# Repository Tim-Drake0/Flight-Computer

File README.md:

# Flight-Computer
Download and open bom.html for interactive BOM.

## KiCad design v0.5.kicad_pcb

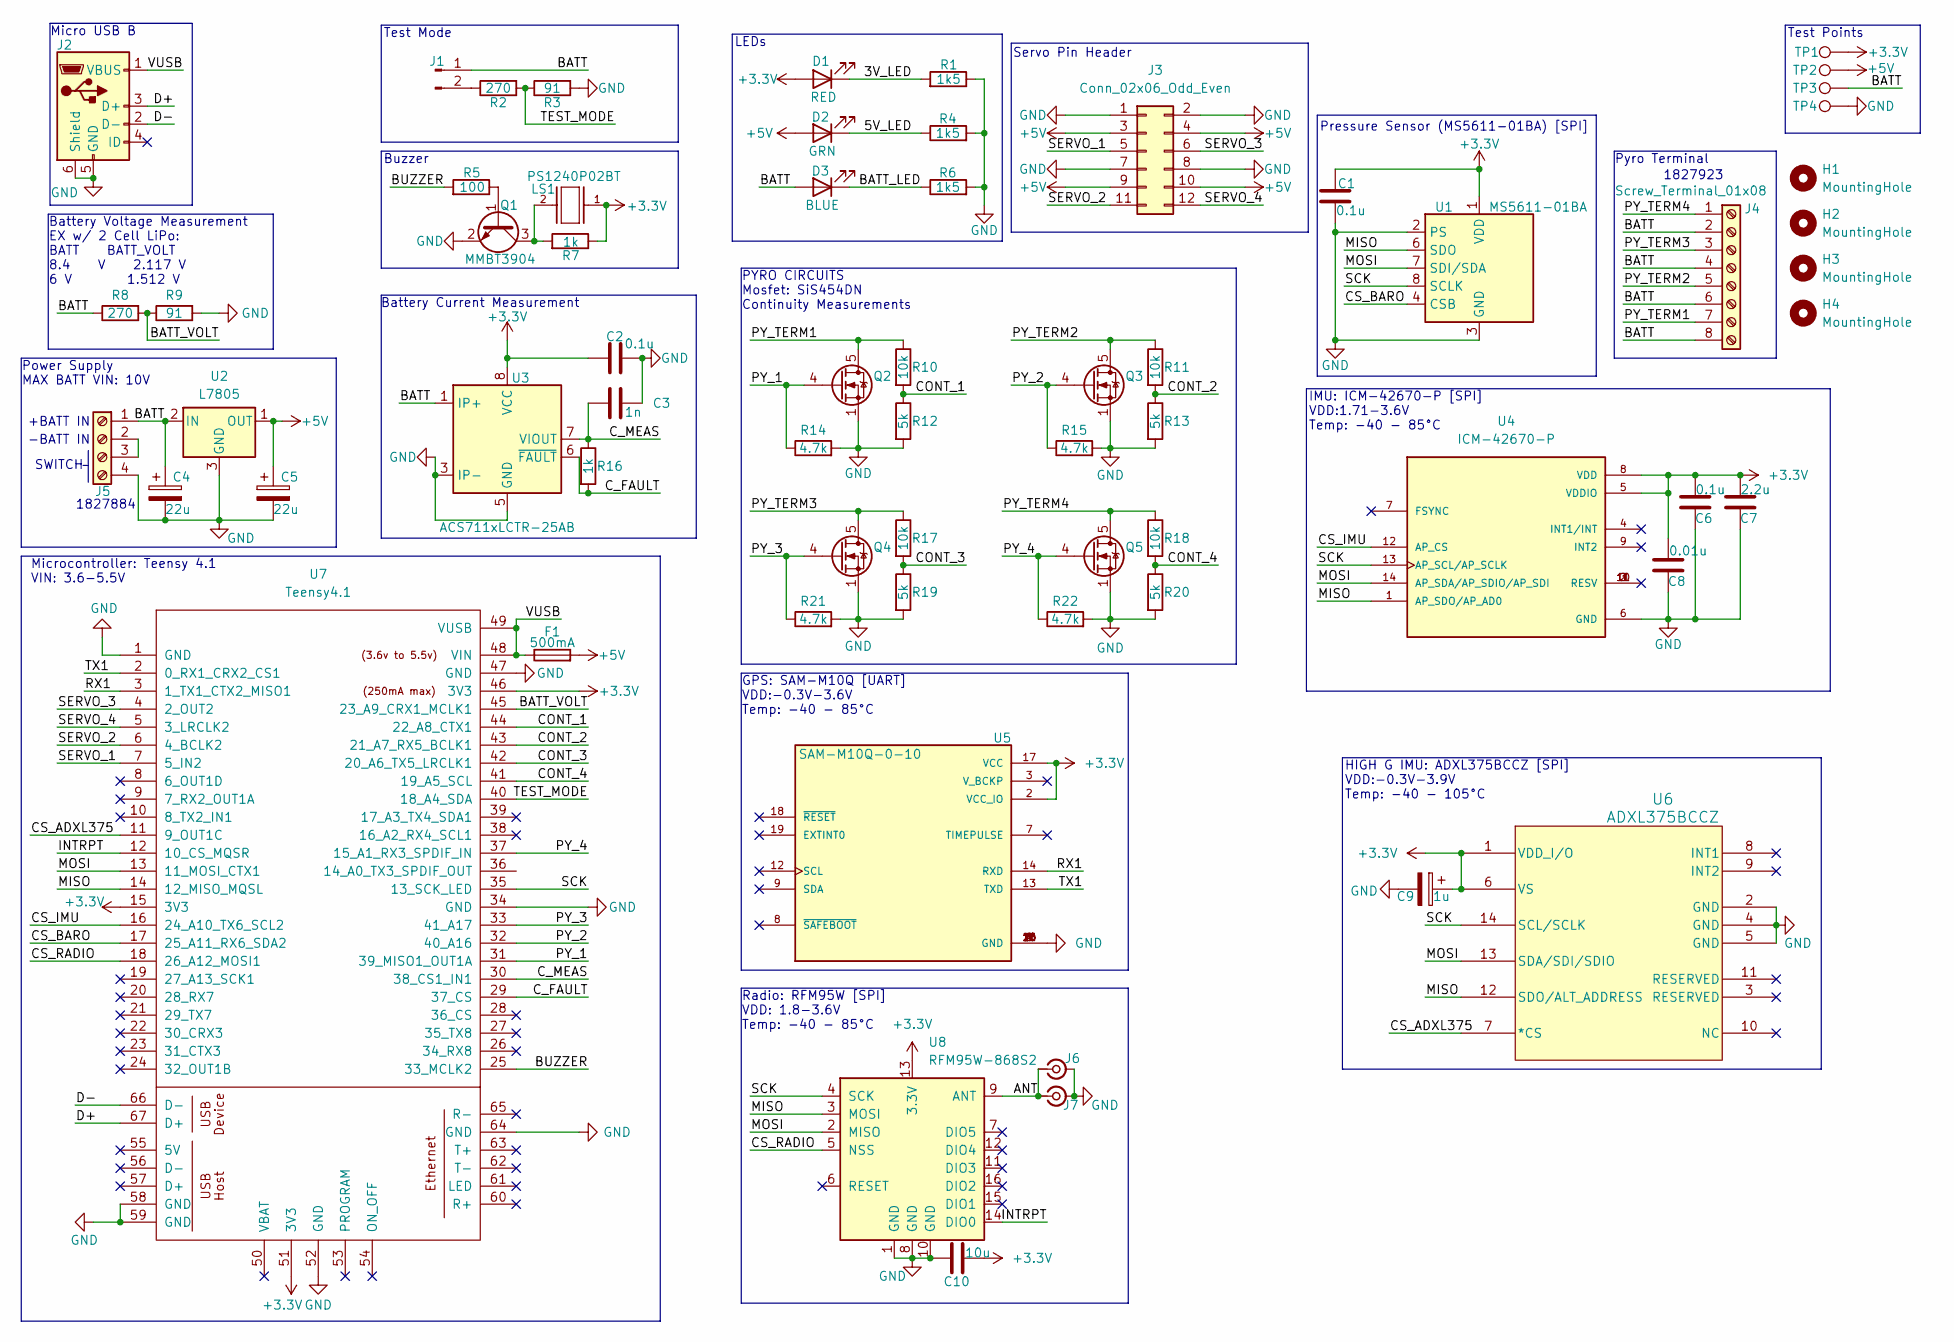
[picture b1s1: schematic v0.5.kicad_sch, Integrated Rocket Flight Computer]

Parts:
C1, C2, C6: 0.1u; C_0805_2012Metric; DigiKey CL21B104KBCNNNC
C3: 1n; C_0805_2012Metric; DigiKey CL21B102KCANNNC
C4, C5: 22u; C_0805_2012Metric; DigiKey TLJN226M010R3800
C7: 2.2u; C_0805_2012Metric; DigiKey CL21B225KPFNNNE
C8: 0.01u; C_0805_2012Metric; DigiKey CL21B103KBANNNC
C9: 1u; C_0805_2012Metric; DigiKey TAJR105K010RNJ
C10: 10u; C_0805_2012Metric_Pad1.18x1.45mm_HandSolder; DigiKey CL21A106KOQNNNE
D1: RED; LED_0603_1608Metric; DigiKey 150060RS75000
D2: GRN; LED_0603_1608Metric; DigiKey 150060GS75000
D3: BLUE; LED_0603_1608Metric; DigiKey 150060BS75000
F1: 500mA; Fuse_0805_2012Metric_Pad1.15x1.40mm_HandSolder; DigiKey F0805B0R50FSTR
H1, H2, H3, H4: MountingHole; MountingHole_2.2mm_M2
J1: Conn_01x02_Pin; PinHeader_1x02_P1.27mm_Horizontal; DigiKey M50-3930242, HMSC-G
J2: USB_B_Micro; USB_Micro-B_Amphenol_10118193-0001LF_Horizontal; DigiKey 10118193-0001LF
J3: Conn_02x06_Odd_Even; PinHeader_2x06_P2.54mm_Vertical; DigiKey PH2-12-UA
J4: Screw_Terminal_01x08; PhoenixContact_MC_1,5_8-GF-3.5_1x08_P3.50mm_Horizontal_Thre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
J5: Screw_Terminal_01x04; PhoenixContact_MC_1,5_4-GF-3.5_1x04_P3.50mm_Horizontal_Thre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
J6: Conn_Coaxial_Small; U.FL_Hirose_U.FL-R-SMT-1_Vertical
J7: Conn_Coaxial_Small; SMA_Samtec_SMA-J-P-H-ST-EM1_EdgeMount
LS1: PS1240P02BT; XDCR_PS1240P02BT; DigiKey PS1240P02BT
Q1: MMBT3904; SOT-23; DigiKey MMBT3904-7-F
Q2, Q3, Q4, Q5: SiS454DN; Vishay_PowerPAK_1212-8_Single; DigiKey SIS454DN-T1-GE3
R1, R4: 1k5; R_0805_2012Metric
R2, R8: 270; R_0805_2012Metric; DigiKey RC0805JR-07270RL
R3, R9: 91; R_0805_2012Metric; DigiKey RC0805FR-0791RL
R5: 100; R_0805_2012Metric; DigiKey RC0805FR-07100RL
R6: 1k5; R_0805_2012Metric; DigiKey RC0805FR-071K5L
R7, R16: 1k; R_0805_2012Metric; DigiKey RC0805FR-071KL
R10, R11, R17, R18: 10k; R_0805_2012Metric_Pad1.20x1.40mm_HandSolder; DigiKey ERJ-6GEYJ103V
R12, R13, R19, R20: 5k; R_0805_2012Metric_Pad1.20x1.40mm_HandSolder; DigiKey CRCW08055K00JNTA
R14, R15, R21, R22: 4.7k; R_0805_2012Metric; DigiKey CRCW08054K70FKEAC
TP1, TP2, TP3, TP4: TestPoint; TestPoint_Keystone_5000-5004_Miniature; DigiKey 5001
U1: MS5611-01BA; LGA-8_3x5mm_P1.25mm; DigiKey MS5611-01BA
U2: L7805; D2PAK_STM; DigiKey L7805ABD2T-TR
U3: ACS711xLCTR-25AB; SOIC-8_3.9x4.9mm_P1.27mm; DigiKey ACS711KLCTR-25AB-T
U4: ICM-42670-P; XDCR_ICM-42670-P; PARTREV 1.1; DigiKey_Part_Number 1428-ICM-42670-PTR-ND
U5: SAM-M10Q-0-10; ublox_SAM-M8Q_HandSolder; PARTREV R07; DigiKey SAM-M10Q-00B
U6: ADXL375BCCZ; LGA_CC-14-1_ADI; DigiKey ADXL375BCCZ
U7: Teensy4.1; Teensy41
U8: RFM95W-868S2; HOPERF_RFM9XW_SMD

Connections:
+3.3V: C1.1, C2.1, C6.2, C7.2, C8.2, C9.1, C10.1, D1.2 (A), LS1.1, R7.1, TP1.1, U1.1 (VDD), U3.8 (VCC), U4.5 (VDDIO), U4.8 (VDD), U5.2 (VCC_IO), U5.17 (VCC), U6.1 (VDD_I/O), U6.6 (VS), U7.15 (3V3), U7.46 (3V3), U7.51 (3V3), U8.13 (3.3V)
+5V: C5.1, D2.2 (A), F1.2, J3.3, J3.4, J3.9, J3.10, TP2.1, U2.1 (OUT)
/3V_LED: D1.1 (K), R1.2
/5V_LED: D2.1 (K), R4.1
/ANT: J6.1 (In), J7.1 (In), U8.9 (ANT)
/BATT: C4.1, D3.2 (A), J1.1, J4.2, J4.4, J4.6, J4.8, J5.1, R8.1, TP3.1, U2.2 (IN), U3.1 (IP+), U3.2 (IP+)
/BATT_LED: D3.1 (K), R6.1
/BATT_VOLT: R8.2, R9.1, U7.45 (23_A9_CRX1_MCLK1)
/BUZZER: R5.2, U7.25 (33_MCLK2)
/CONT_1: R10.2, R12.1, U7.44 (22_A8_CTX1)
/CONT_2: R11.2, R13.1, U7.43 (21_A7_RX5_BCLK1)
/CONT_3: R17.2, R19.1, U7.42 (20_A6_TX5_LRCLK1)
/CONT_4: R18.2, R20.1, U7.41 (19_A5_SCL)
/CS_ADXL375: U6.7 (*CS), U7.11 (9_OUT1C)
/CS_BARO: U1.4 (CSB), U1.5 (CSB), U7.17 (25_A11_RX6_SDA2)
/CS_IMU: U4.12 (AP_CS), U7.16 (24_A10_TX6_SCL2)
/CS_RADIO: U7.18 (26_A12_MOSI1), U8.5 (NSS)
/C_FAULT: R16.2, U3.6 (~FAULT), U7.29 (37_CS)
/C_MEAS: C3.1, R16.1, U3.7 (VIOUT), U7.30 (38_CS1_IN1)
/D+: J2.3 (D+), U7.67 (D+)
/D-: J2.2 (D-), U7.66 (D-)
/INTRPT: U7.12 (10_CS_MQSR), U8.14 (DIO0)
/MISO: U1.6 (SDO), U4.1 (AP_SDO/AP_AD0), U6.12 (SDO/ALT_ADDRESS), U7.14 (12_MISO_MQSL), U8.3 (MOSI)
/MOSI: U1.7 (SDI/SDA), U4.14 (AP_SDA/AP_SDIO/AP_SDI), U6.13 (SDA/SDI/SDIO), U7.13 (11_MOSI_CTX1), U8.2 (MISO)
/PY_1: Q2.4 (G), R14.1, U7.31 (39_MISO1_OUT1A)
/PY_2: Q3.4 (G), R15.1, U7.32 (40_A16)
/PY_3: Q4.4 (G), R21.1, U7.33 (41_A17)
/PY_4: Q5.4 (G), R22.1, U7.37 (15_A1_RX3_SPDIF_IN)
/PY_TERM1: J4.7, Q2.5 (D), R10.1
/PY_TERM2: J4.5, Q3.5 (D), R11.1
/PY_TERM3: J4.3, Q4.5 (D), R17.1
/PY_TERM4: J4.1, Q5.5 (D), R18.1
/RX1: U5.14 (RXD), U7.3 (1_TX1_CTX2_MISO1)
/SCK: U1.8 (SCLK), U4.13 (AP_SCL/AP_SCLK), U6.14 (SCL/SCLK), U7.35 (13_SCK_LED), U8.4 (SCK)
/SERVO_1: J3.5, U7.7 (5_IN2)
/SERVO_2: J3.11, U7.6 (4_BCLK2)
/SERVO_3: J3.6, U7.4 (2_OUT2)
/SERVO_4: J3.12, U7.5 (3_LRCLK2)
/TEST_MODE: R2.2, R3.1, U7.40 (18_A4_SDA)
/TX1: U5.13 (TXD), U7.2 (0_RX1_CRX2_CS1)
/VUSB: F1.1, J2.1 (VBUS), U7.48 (VIN), U7.49 (VUSB)
GND: C1.2, C2.2, C3.2, C4.2, C5.2, C6.1, C7.1, C8.1, C9.2, C10.2, J2.5 (GND), J2.6 (Shield), J3.1, J3.2, J3.7, J3.8, J5.4, J6.2 (Ext), J7.2 (Ext), Q1.2 (E), Q2.1 (S), Q2.2 (S), Q2.3 (S), Q3.1 (S), Q3.2 (S), Q3.3 (S), Q4.1 (S), Q4.2 (S), Q4.3 (S), Q5.1 (S), Q5.2 (S), Q5.3 (S), R1.1, R3.2, R4.2, R6.2, R9.2, R12.2, R13.2, R14.2, R15.2, R19.2, R20.2, R21.2, R22.2, TP4.1, U1.2 (PS), U1.3 (GND), U2.3 (GND), U3.3 (IP-), U3.4 (IP-), U3.5 (GND), U4.6 (GND), U5.1 (GND), U5.4 (GND), U5.5 (GND), U5.6 (GND), U5.10 (GND), U5.11 (GND), U5.15 (GND), U5.16 (GND), U5.20 (GND), U6.2 (GND), U6.4 (GND), U6.5 (GND), U7.1 (GND), U7.34 (GND), U7.47 (GND), U7.52 (GND), U7.58 (GND), U7.59 (GND), U7.64 (GND), U8.1 (GND), U8.8 (GND), U8.10 (GND)
unnamed: J1.2, R2.1
unnamed: J5.2, J5.3
unnamed: Q1.1 (B), R5.1
unnamed: LS1.2, Q1.3 (C), R7.2

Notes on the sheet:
-BATT IN
Power Supply MAX BATT VIN: 10V
1827923
LEDs
Pyro Terminal
IMU: ICM-42670-P [SPI] VDD:1.71-3.6V Temp: -40 - 85°C
Microcontroller: Teensy 4.1 VIN: 3.6-5.5V
GPS: SAM-M10Q [UART] VDD:-0.3V-3.6V Temp: -40 - 85°C
Servo Pin Header
1827884
Battery Current Measurement
SWITCH
Test Mode
HIGH G IMU: ADXL375BCCZ [SPI] VDD:-0.3V-3.9V Temp: -40 - 105°C
Test Points
+BATT IN
Radio: RFM95W [SPI] VDD: 1.8-3.6V Temp: -40 - 85°C
Micro USB B
Pressure Sensor (MS5611-01BA) [SPI]
Battery Voltage Measurement EX w/ 2 Cell LiPo: BATT BATT_VOLT 8.4 V 2.117 V 6 V 1.512 V
PYRO CIRCUITS Mosfet: SiS454DN Continuity Measurements
Buzzer

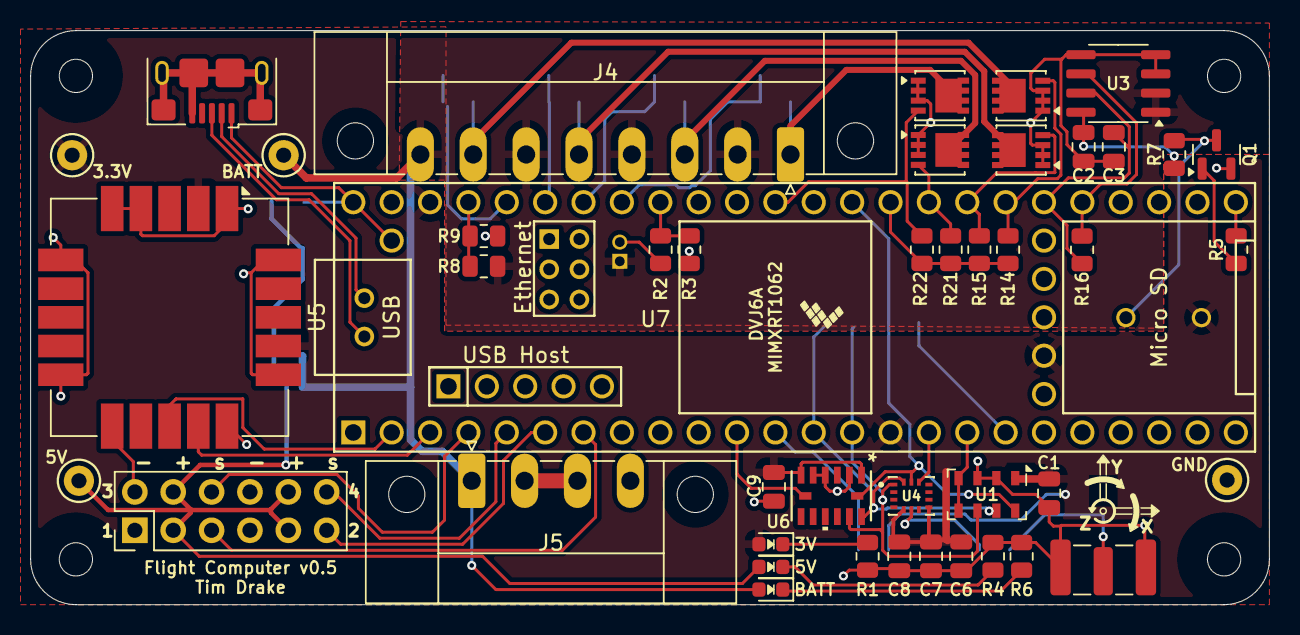
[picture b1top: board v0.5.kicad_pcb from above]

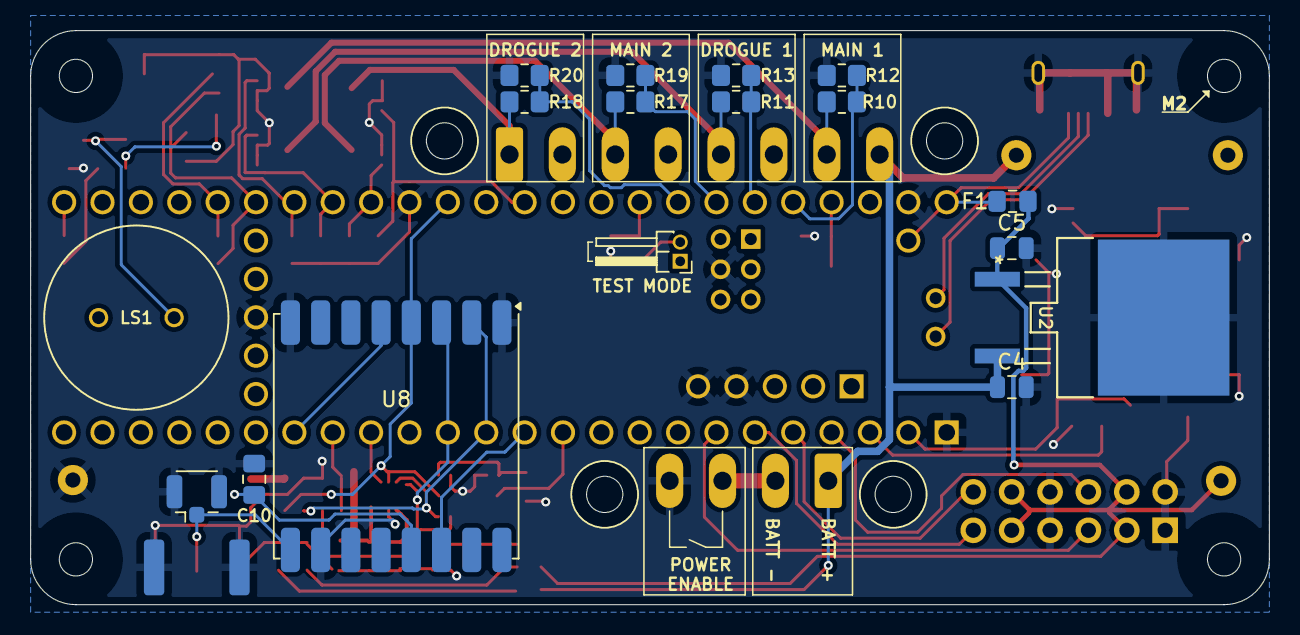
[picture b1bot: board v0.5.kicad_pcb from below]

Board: 2 copper layers, 82.0 x 38.0 mm, 65 parts (17 on the bottom side), 46 nets.

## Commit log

2024-11-09 Add Pictures
2024-11-09 Add Picture Folder
2024-11-09 Edit Pictures
2024-11-10 Added test pin headers. Updated BOM
2024-11-10 Updated BOM
2024-11-10 Using RFM95W radio now instead of RFM69W.
2024-11-10 Ready to buy
2024-11-10 Add gerber files
2024-11-10 Updated gerber files
